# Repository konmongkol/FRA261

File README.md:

# FRA261

## Connector

| Pin | Motor | Encoder | End Effector | Emergency Stop 1 | Emergency Stop 2 |
|-----|----------------|---------|---------|------------------|------------------|
| 1 | VCC |   VCC   | GND |   VCC  |   VCC  |
| 2 | GND |   GND   | SDA |   GND  |   GND  |
| 3 |     | Phase A | SCL | Signal | Signal |
| 4 |     | Phase B | VCC |        |        |

<br>

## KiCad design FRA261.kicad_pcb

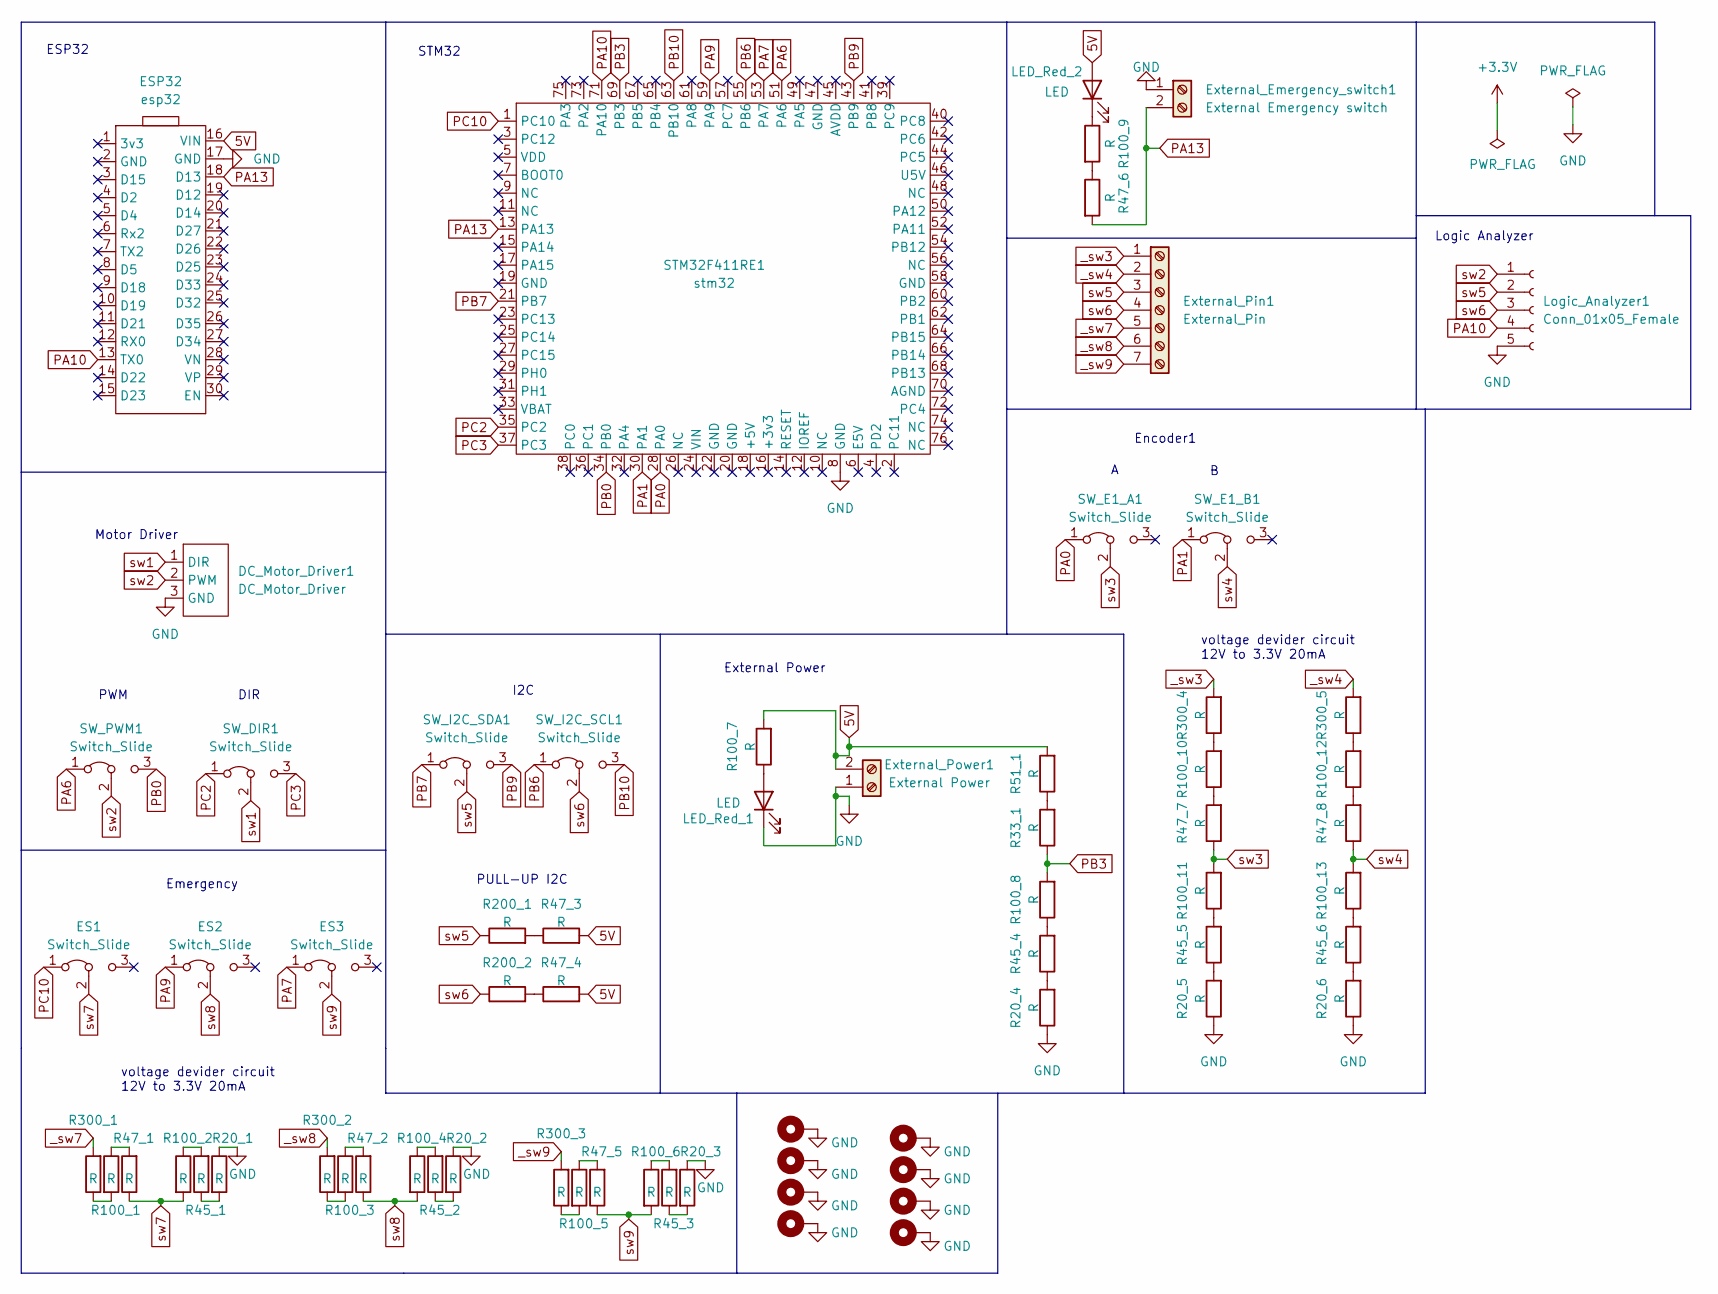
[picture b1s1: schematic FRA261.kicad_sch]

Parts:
DC_Motor_Driver1: DC_Motor_Driver
ES1, ES2, ES3: Switch_Slide; SolderJumper-3_P1.3mm_Bridged12_Pad1.0x1.5mm
ESP32: esp32; Esp32
External_Emergency_switch1: External Emergency switch; TerminalBlock_Phoenix_MKDS-1,5-2-5.08_1x02_P5.08mm_Horizont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
External_Pin1: External_Pin; TerminalBlock_Phoenix_MKDS-1,5-7-5.08_1x07_P5.08mm_Horizont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
External_Power1: External Power; TerminalBlock_Phoenix_MKDS-1,5-2-5.08_1x02_P5.08mm_Horizont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
H1, H2, H3, H4, H5, H6, H7, H8: MountingHole_Pad; MountingHole_3.2mm_M3_DIN965_Pad_TopBottom
LED_Red_1, LED_Red_2: LED; LED_1206_3216Metric
Logic_Analyzer1: Conn_01x05_Female; PinSocket_1x05_P2.54mm_Vertical
R20_1, R20_2, R20_3, R20_4, R20_5, R20_6, R33_1, R45_1, R45_2, R45_3, R45_4, R45_5, R45_6, R47_1, R47_2, R47_3, R47_4, R47_5, R47_6, R47_7, R47_8, R51_1, R100_1, R100_2, R100_3, R100_4, R100_5, R100_6, R100_7, R100_8, R100_9, R100_10, R100_11, R100_12, R100_13, R200_1, R200_2, R300_1, R300_2, R300_3, R300_4, R300_5: R; R_1206_3216Metric
STM32F411RE1: stm32; stm32f411re
SW_DIR1: Switch_Slide; SolderJumper-3_P1.3mm_Bridged12_Pad1.0x1.5mm
SW_E1_A1, SW_E1_B1: Switch_Slide; SolderJumper-3_P1.3mm_Bridged12_Pad1.0x1.5mm
SW_I2C_SCL1, SW_I2C_SDA1: Switch_Slide; SolderJumper-3_P1.3mm_Bridged12_Pad1.0x1.5mm
SW_PWM1: Switch_Slide; SolderJumper-3_P1.3mm_Bridged12_Pad1.0x1.5mm

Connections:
5V: ESP32.16 (VIN), External_Power1.2, LED_Red_2.2 (A), R47_3.2, R47_4.2, R51_1.2, R100_7.2
GND: DC_Motor_Driver1.3 (GND), ESP32.17 (GND), External_Emergency_switch1.1, External_Power1.1, H1.1, H2.1, H3.1, H4.1, H5.1, H6.1, H7.1, H8.1, LED_Red_1.1 (K), Logic_Analyzer1.5, R20_1.1, R20_2.1, R20_3.1, R20_4.1, R20_5.1, R20_6.1, STM32F411RE1.8 (GND)
unnamed: LED_Red_1.2 (A), R100_7.1
unnamed: LED_Red_2.1 (K), R100_9.1
unnamed: R20_1.2, R45_1.1
unnamed: R20_2.2, R45_2.1
unnamed: R20_3.2, R45_3.1
unnamed: R20_4.2, R45_4.1
unnamed: R20_5.2, R45_5.1
unnamed: R20_6.2, R45_6.1
unnamed: R33_1.2, R51_1.1
unnamed: R47_1.2, R100_1.1
unnamed: R100_1.2, R300_1.1
unnamed: R45_1.2, R100_2.1
unnamed: R47_2.2, R100_3.1
unnamed: R100_3.2, R300_2.1
unnamed: R45_2.2, R100_4.1
unnamed: R47_5.2, R100_5.1
unnamed: R100_5.2, R300_3.1
unnamed: R45_3.2, R100_6.1
unnamed: R45_4.2, R100_8.1
unnamed: R47_6.1, R100_9.2
unnamed: R47_7.2, R100_10.1
unnamed: R100_10.2, R300_4.1
unnamed: R45_5.2, R100_11.1
unnamed: R47_8.2, R100_12.1
unnamed: R100_12.2, R300_5.1
unnamed: R45_6.2, R100_13.1
unnamed: R47_3.1, R200_1.2
unnamed: R47_4.1, R200_2.2
PA0: STM32F411RE1.28 (PA0), SW_E1_A1.1 (A)
PA1: STM32F411RE1.30 (PA1), SW_E1_B1.1 (A)
PA6: STM32F411RE1.51 (PA6), SW_PWM1.1 (A)
PA7: ES3.1 (A), STM32F411RE1.53 (PA7)
PA9: ES2.1 (A), STM32F411RE1.59 (PA9)
PA10: ESP32.13 (TX0), Logic_Analyzer1.4, STM32F411RE1.71 (PA10)
PA13: ESP32.18 (D13), External_Emergency_switch1.2, R47_6.2, STM32F411RE1.13 (PA13)
PB0: STM32F411RE1.34 (PB0), SW_PWM1.3 (B)
PB3: R33_1.1, R100_8.2, STM32F411RE1.69 (PB3)
PB6: STM32F411RE1.55 (PB6), SW_I2C_SCL1.1 (A)
PB7: STM32F411RE1.21 (PB7), SW_I2C_SDA1.1 (A)
PB9: STM32F411RE1.43 (PB9), SW_I2C_SDA1.3 (B)
PB10: STM32F411RE1.63 (PB10), SW_I2C_SCL1.3 (B)
PC2: STM32F411RE1.35 (PC2), SW_DIR1.1 (A)
PC3: STM32F411RE1.37 (PC3), SW_DIR1.3 (B)
PC10: ES1.1 (A), STM32F411RE1.1 (PC10)
_sw3: External_Pin1.1, R300_4.2
_sw4: External_Pin1.2, R300_5.2
_sw7: External_Pin1.5, R300_1.2
_sw8: External_Pin1.6, R300_2.2
_sw9: External_Pin1.7, R300_3.2
sw1: DC_Motor_Driver1.1 (DIR), SW_DIR1.2 (C)
sw2: DC_Motor_Driver1.2 (PWM), Logic_Analyzer1.1, SW_PWM1.2 (C)
sw3: R47_7.1, R100_11.2, SW_E1_A1.2 (C)
sw4: R47_8.1, R100_13.2, SW_E1_B1.2 (C)
sw5: External_Pin1.3, Logic_Analyzer1.2, R200_1.1, SW_I2C_SDA1.2 (C)
sw6: External_Pin1.4, Logic_Analyzer1.3, R200_2.1, SW_I2C_SCL1.2 (C)
sw7: ES1.2 (C), R47_1.1, R100_2.2
sw8: ES2.2 (C), R47_2.1, R100_4.2
sw9: ES3.2 (C), R47_5.1, R100_6.2

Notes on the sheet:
Logic Analyzer
Encoder1
DIR
voltage devider circuit 12V to 3.3V 20mA
STM32
Emergency
External Power
PULL-UP I2C
Motor Driver
voltage devider circuit 12V to 3.3V 20mA
PWM
ESP32
I2C

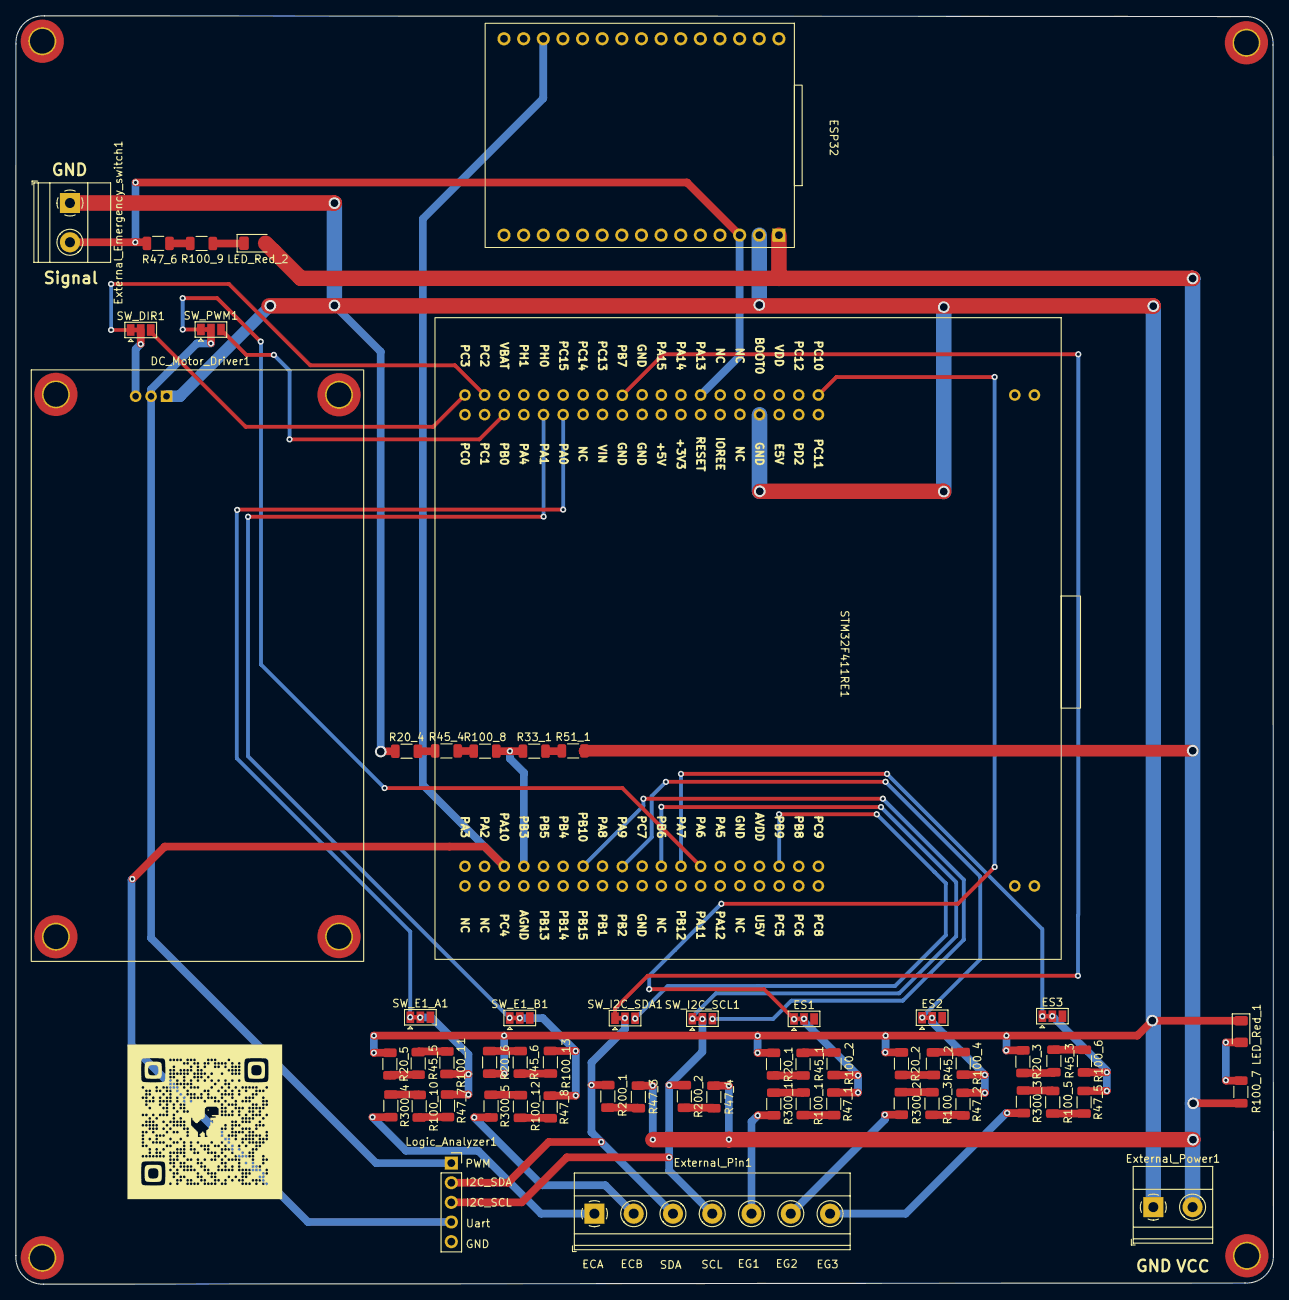
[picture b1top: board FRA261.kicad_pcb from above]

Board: 2 copper layers, 162.7 x 164.1 mm, 68 parts (0 on the bottom side), 60 nets.

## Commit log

2023-04-07 updata
